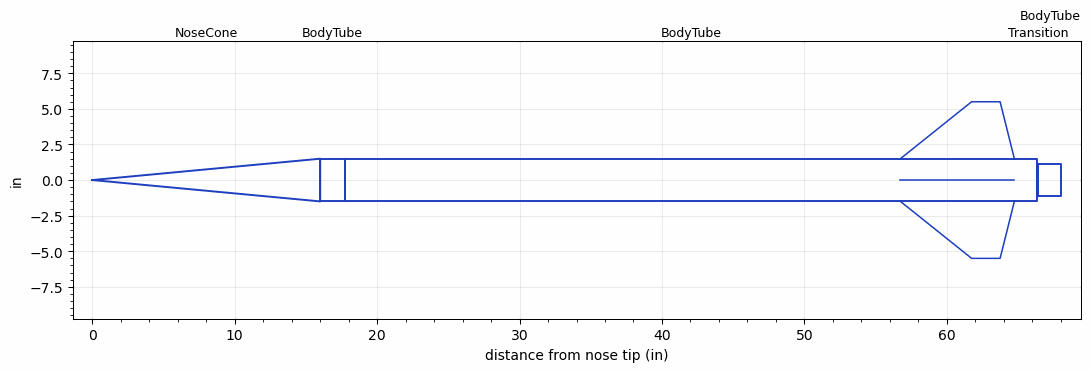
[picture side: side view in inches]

<RASAeroDocument>
 <FileVersion>2</FileVersion>
 <RocketDesign>
  <NoseCone>
   <Length>16</Length>
   <Diameter>3</Diameter>
   <Shape>Conical</Shape>
   <BluntRadius>0.0625</BluntRadius>
   <Location>0</Location>
  </NoseCone>
  <BodyTube>
   <Length>1.75</Length>
   <Diameter>3</Diameter>
   <Location>16</Location>
  </BodyTube>
  <BodyTube>
   <Length>48.6249</Length>
   <Diameter>3</Diameter>
   <Location>17.75</Location>
   <Fin>
    <Count>4</Count>
    <Chord>8</Chord>
    <Span>4</Span>
    <SweepDistance>5</SweepDistance>
    <TipChord>2</TipChord>
    <Thickness>0.1181</Thickness>
    <LERadius>0.01</LERadius>
    <Location>9.625</Location>
    <AirfoilSection>Hexagonal</AirfoilSection>
    <FX1>0.75</FX1>
    <FX3>0.375</FX3>
   </Fin>
  </BodyTube>
  <Transition>
   <Length>0.0625</Length>
   <Diameter>2.25</Diameter>
   <Location>66.3749</Location>
   <RearDiameter>2.25</RearDiameter>
  </Transition>
  <BodyTube>
   <Length>1.6</Length>
   <Diameter>2.25</Diameter>
   <Location>66.4374</Location>
  </BodyTube>
  <Surface>Camouflage Paint</Surface>
  <ModifiedBarrowman>True</ModifiedBarrowman>
  <Turbulence>True</Turbulence>
  <UseBooster1>False</UseBooster1>
  <UseBooster2>False</UseBooster2>
 </RocketDesign>
 <LaunchSite>
  <Altitude>2000</Altitude>
  <Pressure>29.92</Pressure>
  <RodAngle>2</RodAngle>
  <RodLength>10</RodLength>
  <Temperature>59</Temperature>
  <WindSpeed>4.47</WindSpeed>
 </LaunchSite>
 <Recovery>
  <Altitude1>0</Altitude1>
  <Altitude2>0</Altitude2>
  <DeviceType1>None</DeviceType1>
  <DeviceType2>None</DeviceType2>
  <Event1>False</Event1>
  <Event2>False</Event2>
  <Size1>0</Size1>
  <Size2>0</Size2>
  <EventType1>None</EventType1>
  <EventType2>None</EventType2>
  <CD1>0</CD1>
  <CD2>0</CD2>
 </Recovery>
 <SimulationList>
  <Simulation>
   <SustainerEngine>M2459  (boostka)</SustainerEngine>
   <SustainerLaunchWt>19</SustainerLaunchWt>
   <SustainerNozzleDiameter>1.875</SustainerNozzleDiameter>
   <SustainerCG>41.99</SustainerCG>
   <SustainerIgnitionDelay>0</SustainerIgnitionDelay>
   <Booster1SeparationDelay>0</Booster1SeparationDelay>
   <Booster1IgnitionDelay>0</Booster1IgnitionDelay>
   <IncludeBooster1>False</IncludeBooster1>
   <Booster2Delay>0</Booster2Delay>
   <IncludeBooster2>False</IncludeBooster2>
   <TimetoApogee>37.12978</TimetoApogee>
   <MaxAltitude>30101.53</MaxAltitude>
   <MaxVelocity>2722.242</MaxVelocity>
  </Simulation>
 </SimulationList>
</RASAeroDocument>
